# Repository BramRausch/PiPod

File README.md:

# PiPod
PiPod Hardware and Software

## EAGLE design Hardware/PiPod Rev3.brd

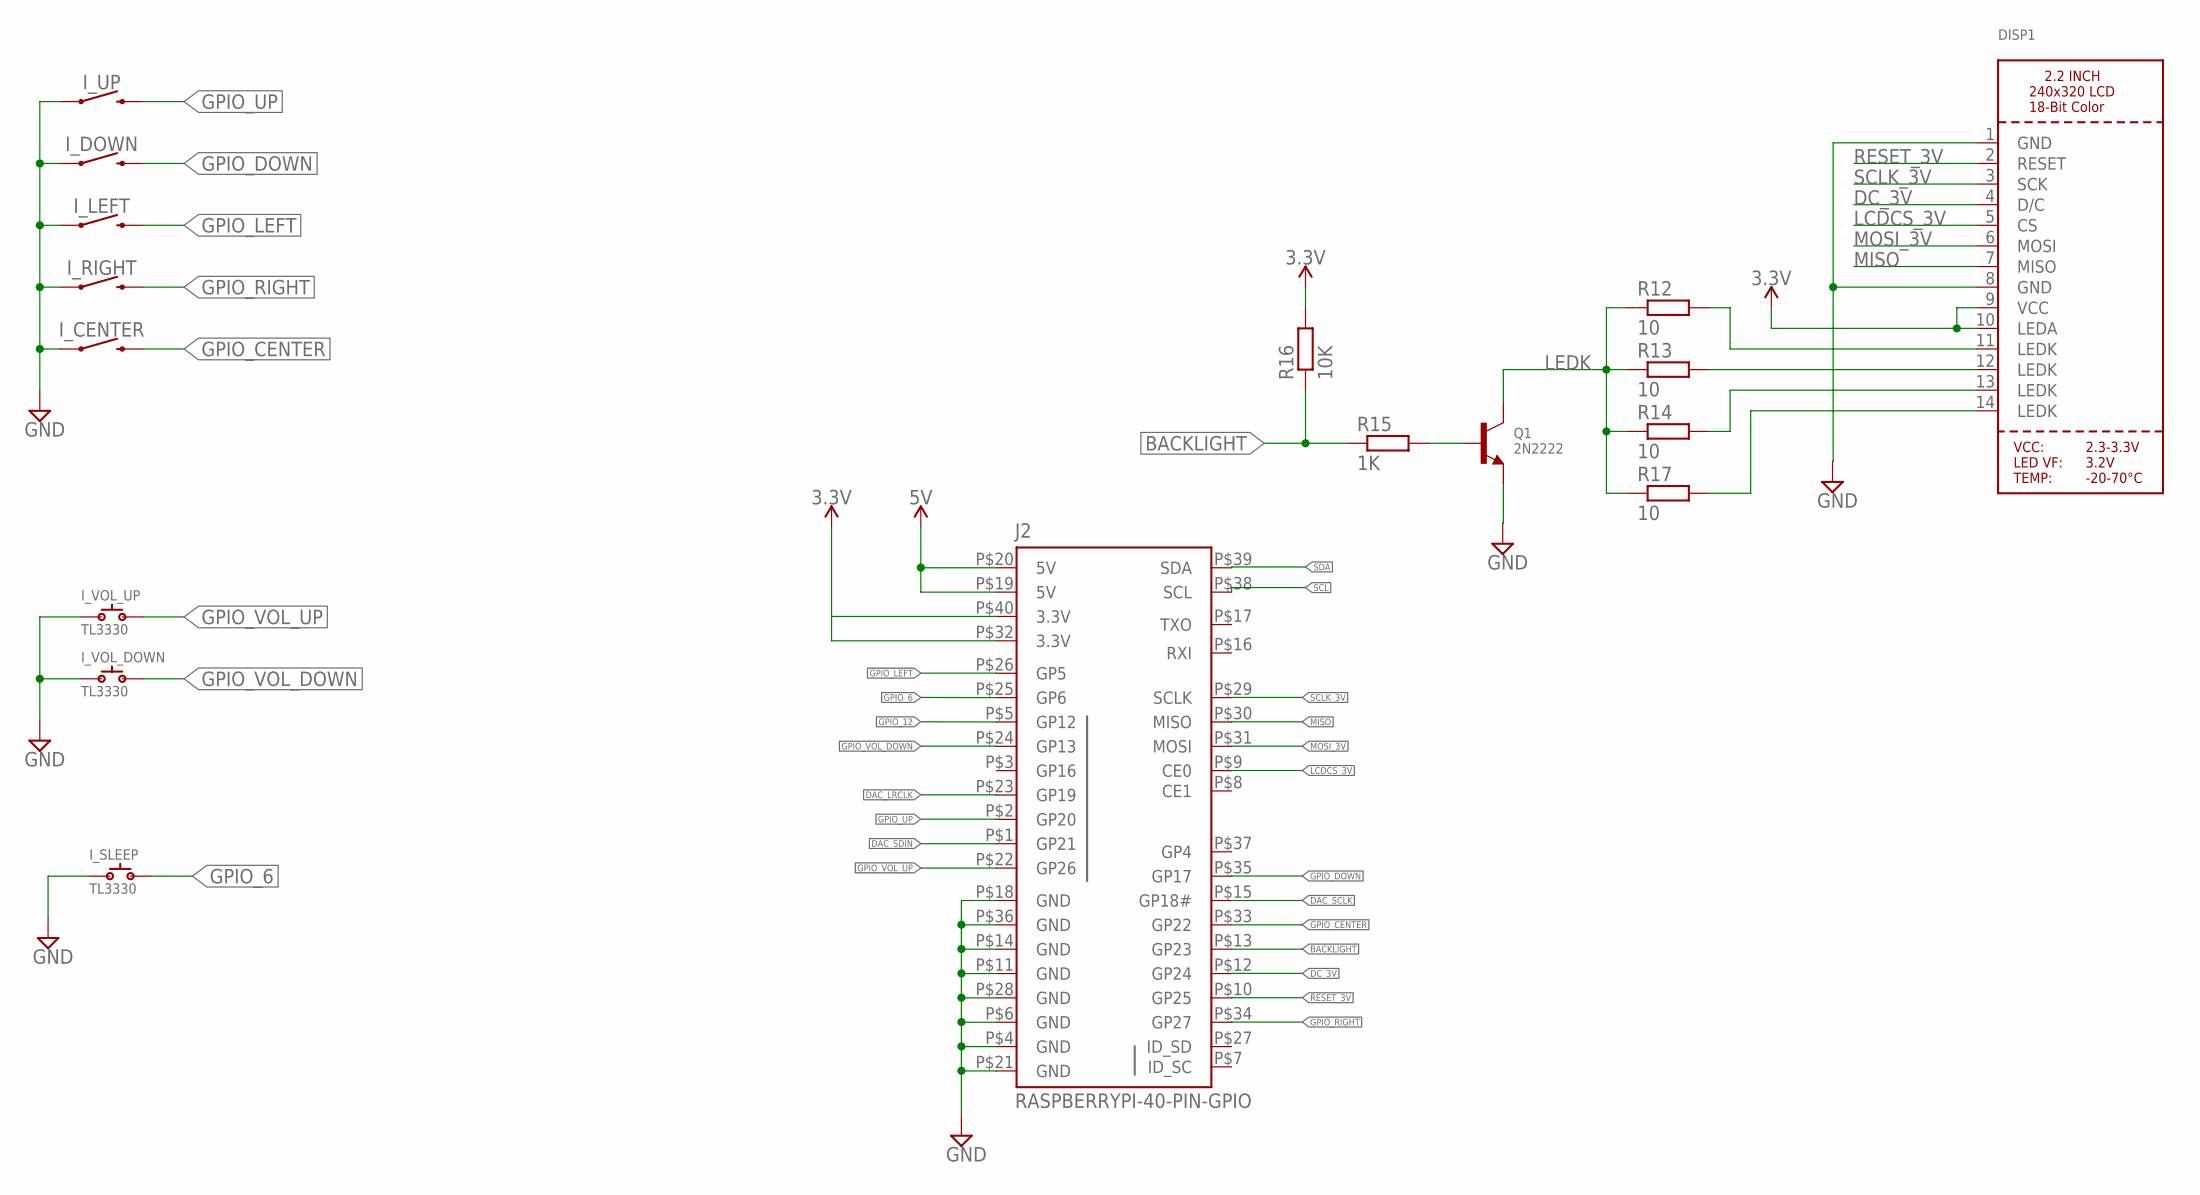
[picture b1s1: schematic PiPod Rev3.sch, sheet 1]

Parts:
DISP1: DISP_LCD_TM022HDH26; TM022HDH26_2.2IN_LCD
I_CENTER: MOMENTARY-SWITCH-SPST-SMD-5.2-REDUNDANT; TACTILE_SWITCH_SMD_5.2MM
I_DOWN: MOMENTARY-SWITCH-SPST-SMD-5.2-REDUNDANT; TACTILE_SWITCH_SMD_5.2MM
I_LEFT: MOMENTARY-SWITCH-SPST-SMD-5.2-REDUNDANT; TACTILE_SWITCH_SMD_5.2MM
I_RIGHT: MOMENTARY-SWITCH-SPST-SMD-5.2-REDUNDANT; TACTILE_SWITCH_SMD_5.2MM
I_SLEEP: TL3330
I_UP: MOMENTARY-SWITCH-SPST-SMD-5.2-REDUNDANT; TACTILE_SWITCH_SMD_5.2MM
I_VOL_DOWN: TL3330
I_VOL_UP: TL3330
J2: RASPBERRYPI-40-PIN-GPIO; 2X20_SMD
Q1: 2N2222; SOT23-WIDE
R12, R13, R14, R17: 10; R0805
R15: 1K; R0805
R16: 10K; R0805

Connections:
3.3V: DISP1.9 (VCC), DISP1.10 (LEDA), J2.P$32 (3.3V), J2.P$40 (3.3V), R16.2; also elsewhere on the board
5V: J2.P$19 (5V), J2.P$20 (5V); also elsewhere on the board
BACKLIGHT: J2.P$13 (GP23), R15.1, R16.1
DAC_LRCLK: J2.P$23 (GP19); also elsewhere on the board
DAC_SCLK: J2.P$15 (GP18#); also elsewhere on the board
DAC_SDIN: J2.P$1 (GP21); also elsewhere on the board
DC_3V: DISP1.4 (D/C), J2.P$12 (GP24)
GND: DISP1.1 (GND), DISP1.8 (GND), I_CENTER.1, I_CENTER.2 (1), I_DOWN.1, I_DOWN.2 (1), I_LEFT.1, I_LEFT.2 (1), I_RIGHT.1, I_RIGHT.2 (1), I_SLEEP.1, I_UP.1, I_UP.2 (1), I_VOL_DOWN.1, I_VOL_UP.1, J2.P$4 (GND), J2.P$6 (GND), J2.P$11 (GND), J2.P$14 (GND), J2.P$18 (GND), J2.P$21 (GND), J2.P$28 (GND), J2.P$36 (GND), Q1.2 (E); also elsewhere on the board
GPIO_6: I_SLEEP.2, J2.P$25 (GP6)
GPIO_12: J2.P$5 (GP12)
GPIO_CENTER: I_CENTER.3 (2), I_CENTER.4 (2), J2.P$33 (GP22)
GPIO_DOWN: I_DOWN.3 (2), I_DOWN.4 (2), J2.P$35 (GP17)
GPIO_LEFT: I_LEFT.3 (2), I_LEFT.4 (2), J2.P$26 (GP5)
GPIO_RIGHT: I_RIGHT.3 (2), I_RIGHT.4 (2), J2.P$34 (GP27)
GPIO_UP: I_UP.3 (2), I_UP.4 (2), J2.P$2 (GP20)
GPIO_VOL_DOWN: I_VOL_DOWN.2, J2.P$24 (GP13)
GPIO_VOL_UP: I_VOL_UP.2, J2.P$22 (GP26)
LCDCS_3V: DISP1.5 (CS), J2.P$9 (CE0)
LEDK: Q1.3 (C), R12.1, R13.1, R14.1, R17.1
MISO: DISP1.7 (MISO), J2.P$30 (MISO)
MOSI_3V: DISP1.6 (MOSI), J2.P$31 (MOSI)
unnamed: DISP1.11 (LEDK), R12.2
unnamed: DISP1.12 (LEDK), R13.2
unnamed: DISP1.13 (LEDK), R14.2
unnamed: Q1.1 (B), R15.2
unnamed: DISP1.14 (LEDK), R17.2
RESET_3V: DISP1.2 (RESET), J2.P$10 (GP25)
SCL: J2.P$38 (SCL); also elsewhere on the board
SCLK_3V: DISP1.3 (SCK), J2.P$29 (SCLK)
SDA: J2.P$39 (SDA); also elsewhere on the board

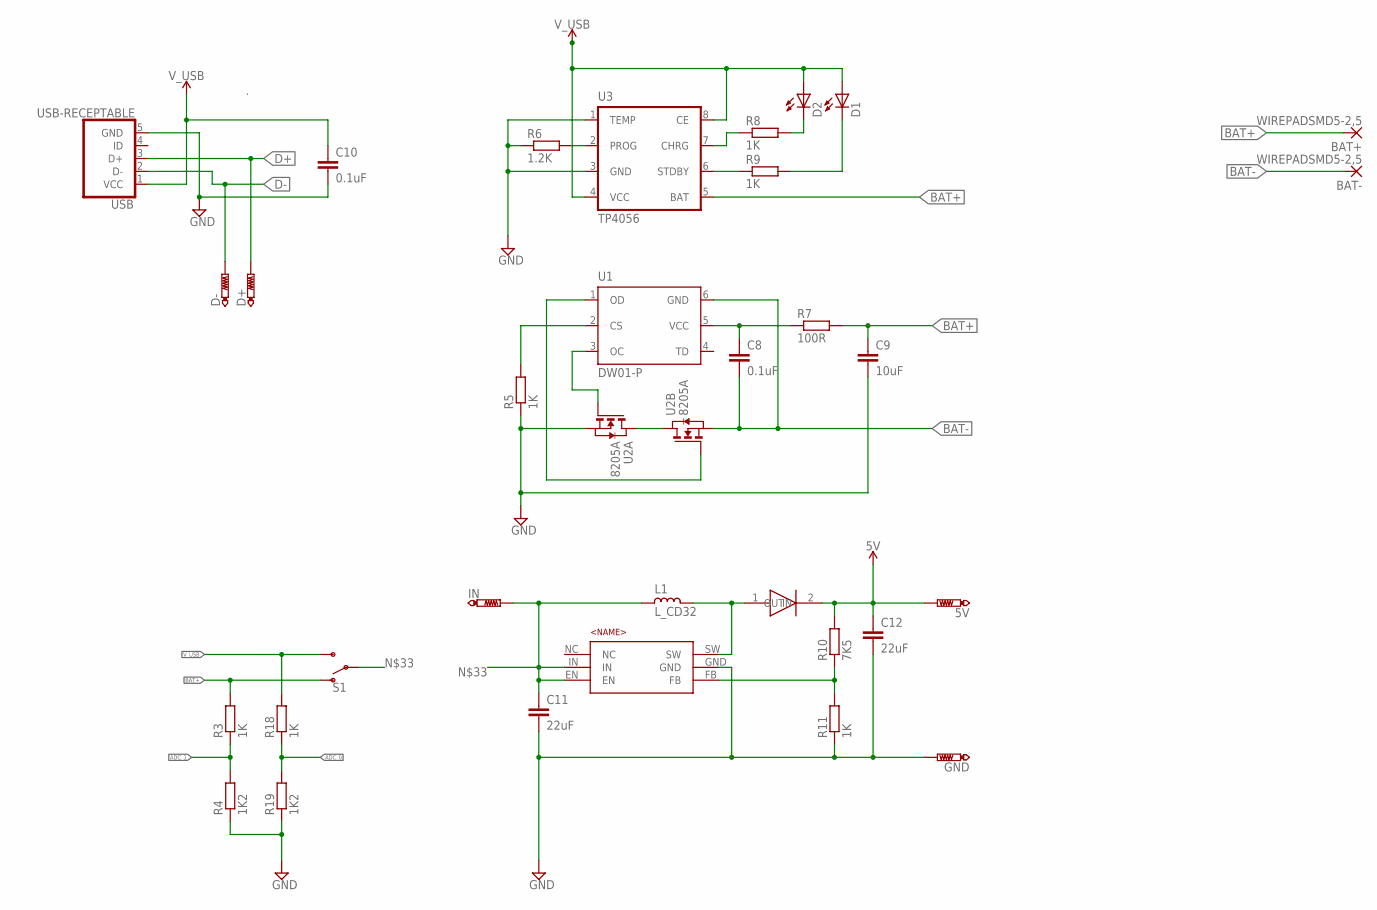
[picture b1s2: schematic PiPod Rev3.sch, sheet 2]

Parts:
5V: PTR1B2,54; B2,54
BAT+: WIREPADSMD5-2,5; 5-2,5
BAT-: WIREPADSMD5-2,5; 5-2,5
C8, C10: 0.1uF; C1206K
C9: 10uF; C1206K
C11, C12: 22uF; C0805K
D1, D2: LEDCHIPLED_0805; CHIPLED_0805
D+: PTR1TP15R; TP15R
D-: PTR1TP15R; TP15R
GND: PTR1B2,54; B2,54
IN: PTR1B2,54; B2,54
L1: L_CD32; CD32
R3, R11, R18: 1K; R0805
R4, R19: 1K2; R0805
R5, R8, R9: 1K; M0805
R6: 1.2K; M0805
R7: 100R; M0805
R10: 7K5; R0805
S1: SWITCH-SPDT-PTH-11.6X4.0MM; SWITCH_SPDT_PTH_11.6X4.0MM
U1: DW01-P; SOT23-6L
U2: 8205A; TSSOP8
U3: TP4056; SO08
U6: MT3608; SOT23-6
U$9: SMA-SS34
USB: USB-RECEPTABLE; FCI-10103594-0001LF

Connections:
5V: 5V.TP, C12.1, R10.2, U$9.2 (OUT); also elsewhere on the board
ADC_0: R18.1, R19.2; also elsewhere on the board
ADC_1: R3.1, R4.2; also elsewhere on the board
BAT+: BAT+.1, C9.1, R3.2, R7.2, S1.1 (O), U3.5 (BAT)
BAT-: BAT-.1, C8.2, U1.6 (GND), U2.6 (S), U2.7 (S)
D+: D+.TP, USB.3 (D+)
D-: D-.TP, USB.2 (D-)
GND: C9.2, C10.2, C11.2, C12.2, GND.TP, R4.1, R5.1, R6.1, R11.1, R19.1, U2.2 (S), U2.3 (S), U3.1 (TEMP), U3.3 (GND), U6.GND, USB.5 (GND); also elsewhere on the board
unnamed: U2.1 (D), U2.8 (D)
unnamed: U1.1 (OD), U2.5 (G)
unnamed: R5.2, U1.2 (CS)
unnamed: R6.2, U3.2 (PROG)
unnamed: U1.3 (OC), U2.4 (G)
unnamed: R9.1, U3.6 (STDBY)
unnamed: C8.1, R7.1, U1.5 (VCC)
unnamed: D2.C, R8.2
unnamed: D1.C, R9.2
unnamed: R8.1, U3.7 (CHRG)
unnamed: L1.1, U6.SW, U$9.1 (IN)
unnamed: R10.1, R11.2, U6.FB
unnamed: C11.1, IN.TP, L1.2, S1.2, U6.EN, U6.IN
V_USB: C10.1, D1.A, D2.A, R18.2, S1.3 (S), U3.4 (VCC), U3.8 (CE), USB.1 (VCC)

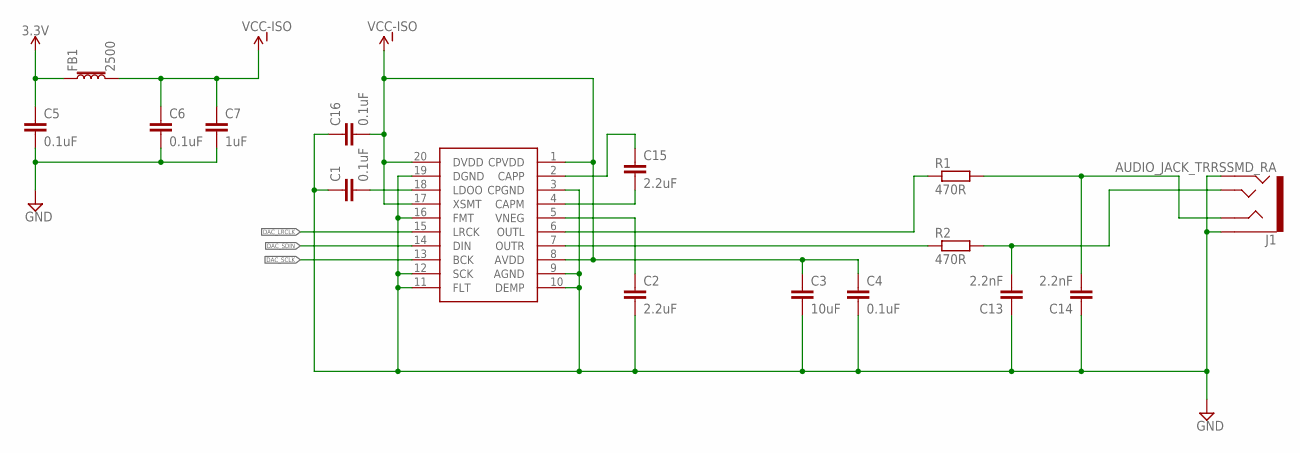
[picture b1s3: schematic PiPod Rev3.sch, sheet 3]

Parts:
C1, C4, C5, C6, C16: 0.1uF; C0805K
C2, C15: 2.2uF; C0805K
C3: 10uF; C0805K
C7: 1uF; C0805K
C13, C14: 2.2nF; C0805K
FB1: 2500; 0603
J1: AUDIO_JACK_TRRSSMD_RA; AUDIO_JACK_3.5MM_TRRS_SMD_RA
R1, R2: 470R; R0805
U5: PCM5102; TSSOP20

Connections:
3.3V: C5.1, FB1.1; also elsewhere on the board
DAC_LRCLK: U5.15 (LRCK); also elsewhere on the board
DAC_SCLK: U5.13 (BCK); also elsewhere on the board
DAC_SDIN: U5.14 (DIN); also elsewhere on the board
GND: C1.1, C2.2, C3.2, C4.2, C5.2, C6.2, C7.2, C13.1, C14.1, C16.1, J1.EARTH, J1.RING2, U5.3 (CPGND), U5.9 (AGND), U5.10 (DEMP), U5.11 (FLT), U5.12 (SCK), U5.16 (FMT), U5.19 (DGND); also elsewhere on the board
unnamed: C1.2, U5.18 (LDOO)
unnamed: C2.1, U5.5 (VNEG)
unnamed: C15.2, U5.4 (CAPM)
unnamed: R2.1, U5.7 (OUTR)
unnamed: R1.1, U5.6 (OUTL)
unnamed: C15.1, U5.2 (CAPP)
unnamed: C13.2, J1.TIP, R2.2
unnamed: C14.2, J1.RING1, R1.2
VCC-ISO: C3.1, C4.1, C6.1, C7.1, C16.2, FB1.2, U5.1 (CPVDD), U5.8 (AVDD), U5.17 (XSMT), U5.20 (DVDD); also elsewhere on the board

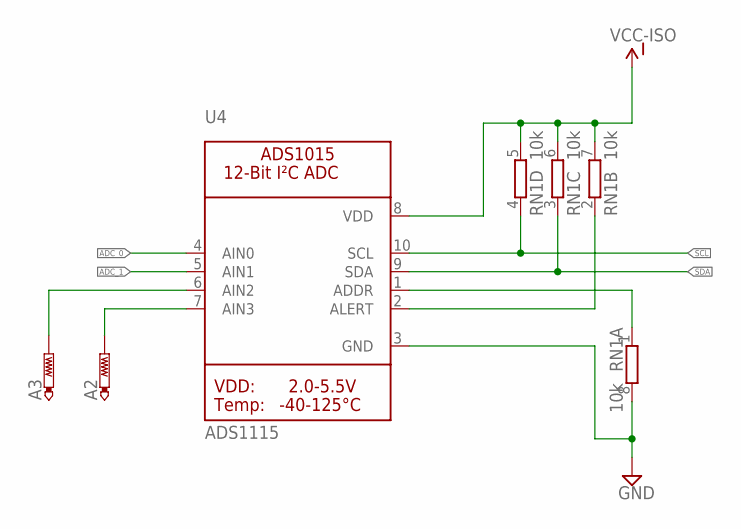
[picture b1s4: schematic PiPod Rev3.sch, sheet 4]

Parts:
A2, A3: PTR1TP15R; TP15R
RN1: 10k; 0603-ARC
U4: ADS1115; MICROBUILDER_MSOP10

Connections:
ADC_0: U4.4 (AIN0); also elsewhere on the board
ADC_1: U4.5 (AIN1); also elsewhere on the board
GND: RN1.8 (2), U4.3 (GND); also elsewhere on the board
unnamed: A2.TP, U4.7 (AIN3)
unnamed: RN1.1, U4.1 (ADDR)
unnamed: RN1.2 (1), U4.2 (ALERT)
unnamed: A3.TP, U4.6 (AIN2)
SCL: RN1.4 (1), U4.10 (SCL); also elsewhere on the board
SDA: RN1.3 (1), U4.9 (SDA); also elsewhere on the board
VCC-ISO: RN1.5 (2), RN1.6 (2), RN1.7 (2), U4.8 (VDD); also elsewhere on the board

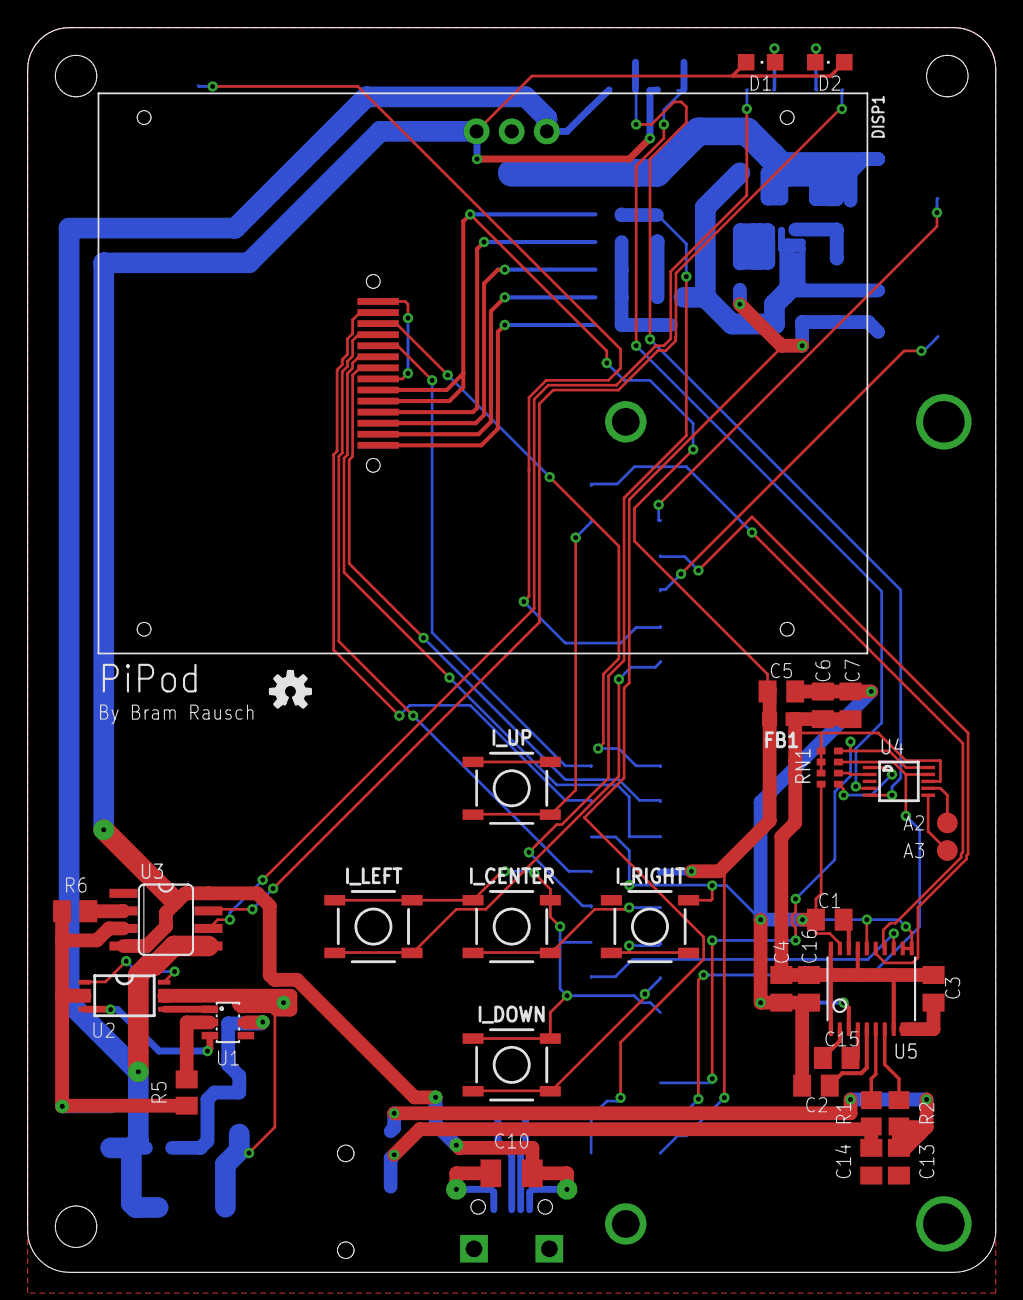
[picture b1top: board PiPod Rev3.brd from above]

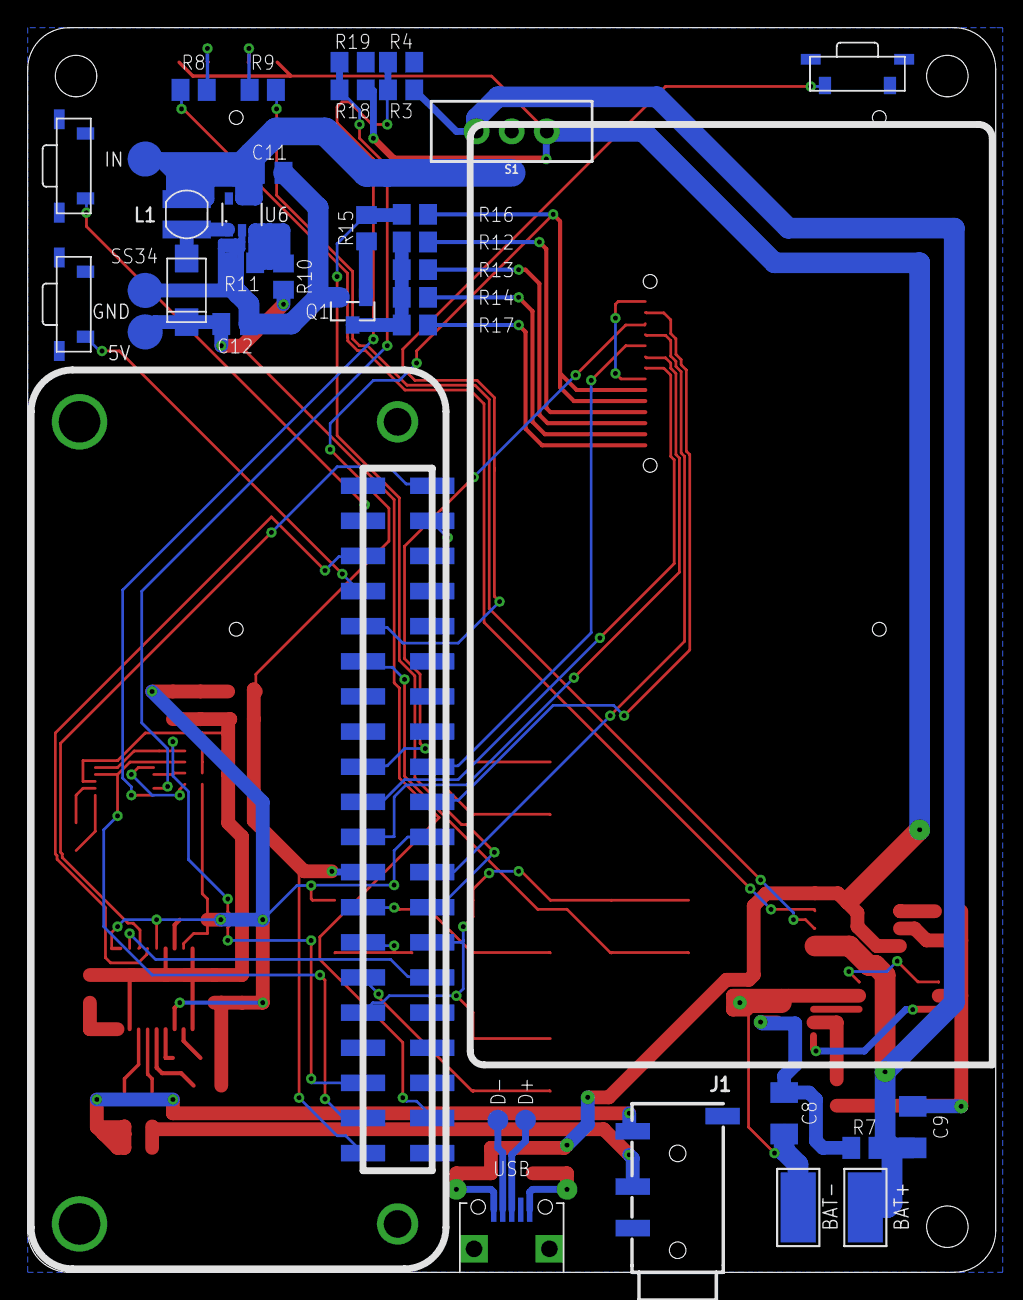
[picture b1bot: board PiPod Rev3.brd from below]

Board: 2 copper layers, 70.0 x 90.0 mm, 71 parts (37 on the bottom side), 62 nets.

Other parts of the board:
E$1: OSHW-LOGO-S

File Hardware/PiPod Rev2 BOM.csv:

"Qty";"Value";"Device";"Package";"Parts";"Description";"MF";"MPN";"OC_FARNELL";"OC_NEWARK";"PROD_ID";"SF_ID";"SF_SKU";"SPICEPREFIX";"TP_SIGNAL_NAME";"VALUE";
"1";"";"DISP_LCD_TM022HDH26";"TM022HDH26_2.2IN_LCD";"DISP1";"TM022HDH26 2.2 Inch 240x320 18-bit LCD - ILI9340C Controller";"";"";"";"";"";"";"";"";"";"";
"2";"";"LEDCHIPLED_0805";"CHIPLED_0805";"D1, D2";"LED";"";"";"";"";"";"";"";"";"";"";
"1";"";"SWITCH-SPDT-PTH-11.6X4.0MM";"SWITCH_SPDT_PTH_11.6X4.0MM";"S1";"Single Pole, Double Throw (SPDT) Switch";"";"";"";"";"SWCH-08261";"";"COM-00102";"";"";"";
"5";"0.1uF";"C-EUC0805K";"C0805K";"C1, C4, C5, C6, C16";"CAPACITOR, European symbol";"";"";"";"";"";"";"";"C";"";"";
"2";"0.1uF";"C-EUC1206K";"C1206K";"C8, C10";"CAPACITOR, European symbol";"";"";"";"";"";"";"";"";"";"";
"1";"1.2K";"R-EU_M0805";"M0805";"R6";"RESISTOR, European symbol";"";"";"";"";"";"";"";"";"";"";
"4";"10";"R-EU_R0805";"R0805";"R12, R13, R14, R17";"RESISTOR, European symbol";"";"";"";"";"";"";"";"";"";"";
"1";"100R";"R-EU_M0805";"M0805";"R7";"RESISTOR, European symbol";"";"";"";"";"";"";"";"";"";"";
"1";"10K";"R-EU_R0805";"R0805";"R16";"RESISTOR, European symbol";"";"";"";"";"";"";"";"";"";"";
"1";"10k";"4R-N0603-ARC";"0603-ARC";"RN1";"Array Chip Resistor";"";"";"unknown";"unknown";"";"";"";"";"";"";
"1";"10uF";"C-EUC0805K";"C0805K";"C3";"CAPACITOR, European symbol";"";"";"";"";"";"";"";"C";"";"";
"1";"10uF";"C-EUC1206K";"C1206K";"C9";"CAPACITOR, European symbol";"";"";"";"";"";"";"";"";"";"";
"3";"1K";"R-EU_M0805";"M0805";"R5, R8, R9";"RESISTOR, European symbol";"";"";"";"";"";"";"";"";"";"";
"4";"1K";"R-EU_R0805";"R0805";"R3, R11, R15, R18";"RESISTOR, European symbol";"";"";"";"";"";"";"";"";"";"";
"2";"1K2";"R-EU_R0805";"R0805";"R4, R19";"RESISTOR, European symbol";"";"";"";"";"";"";"";"";"";"";
"1";"1uF";"C-EUC0805K";"C0805K";"C7";"CAPACITOR, European symbol";"";"";"";"";"";"";"";"C";"";"";
"2";"2.2nF";"C-EUC0805K";"C0805K";"C13, C14";"CAPACITOR, European symbol";"";"";"";"";"";"";"";"C";"";"";
"2";"2.2uF";"C-EUC0805K";"C0805K";"C2, C15";"CAPACITOR, European symbol";"";"";"";"";"";"";"";"C";"";"";
"2";"22uF";"C-EUC0805K";"C0805K";"C11, C12";"CAPACITOR, European symbol";"";"";"";"";"";"";"";"";"";"";
"1";"2500";"FERRITE_BEAD-0603";"0603";"FB1";"Ferrite Bead (blocks, cores, rings, chokes, etc.)";"";"";"";"";"NDUC-07859";"";"";"";"";"30O/1.8A";
"1";"2N2222";"TRANSISTOR_NPNWIDE";"SOT23-WIDE";"Q1";"NPN Transistor";"";"";"";"";"";"";"";"";"";"";
"2";"470R";"R-EU_R0805";"R0805";"R1, R2";"RESISTOR, European symbol";"";"";"";"";"";"";"";"";"";"";
"1";"7K5";"R-EU_R0805";"R0805";"R10";"RESISTOR, European symbol";"";"";"";"";"";"";"";"";"";"";
"1";"8205A";"8205A";"TSSOP8";"U2";"DUAL N-CHANNEL MOSFET";"";"";"";"";"";"";"";"";"";"";
"1";"ADS1115";"MICROBUILDER_ADC_ADS1015";"MICROBUILDER_MSOP10";"U4";"ADS1015 - 12-bit 4-Channel I2C ADC with Internal PGA";"";"";"";"";"";"";"";"";"";"";
"1";"AUDIO_JACK_TRRSSMD_RA";"AUDIO_JACK_TRRSSMD_RA";"AUDIO_JACK_3.5MM_TRRS_SMD_RA";"J1";"Audio Jack - 3.5mm TRRS (SMD)";"";"";"";"";"CONN-10676";"PRT-12639";"";"";"";"";
"1";"DW01-P";"DW01-P";"SOT23-6L";"U1";"One Cell Lithium-ion/Polymer Battery Protection IC";"";"";"";"";"";"";"";"";"";"";
"1";"L_CD32";"L_CD32";"CD32";"L1";"INDUCTOR";"";"";"";"";"";"";"";"";"";"";
"5";"MOMENTARY-SWITCH-SPST-SMD-5.2-REDUNDANT";"MOMENTARY-SWITCH-SPST-SMD-5.2-REDUNDANT";"TACTILE_SWITCH_SMD_5.2MM";"I_CENTER, I_DOWN, I_LEFT, I_RIGHT, I_UP";"Momentary Switch (Pushbutton) - SPST";"";"";"";"";"SWCH-08247";"";"COM-08720";"";"";"";
"1";"MT3608";"MT3608";"SOT23-6";"U6";"";"";"";"";"";"";"";"";"";"";"";
"1";"PCM5102";"PCM5102";"TSSOP20";"U5";"";"";"";"";"";"";"";"";"";"";"";
"3";"PTR1B2,54";"PTR1B2,54";"B2,54";"5V, GND, IN";"TEST PIN";"";"";"";"";"";"";"";"";"";"";
"4";"PTR1TP15R";"PTR1TP15R";"TP15R";"A2, A3, D+, D-";"TEST PIN";"";"";"";"";"";"";"";"";"";"";
"1";"RASPBERRYPI-40-PIN-GPIO";"RASPBERRYPI-40-PIN-GPIO";"2X20_SMD";"J2";"Raspberry Pi GPIO Header";"";"";"";"";"";"";"";"";"";"";
"1";"SMA-SS34";"SMA-SS34";"SMA-SS34";"U$9";"";"";"";"";"";"";"";"";"";"";"";
"3";"TL3330";"TL3330";"TL3330";"I_SLEEP, I_VOL_DOWN, I_VOL_UP";"";"";"";"";"";"";"";"";"";"";"";
"1";"TP4056";"TP4056";"SO08";"U3";"1A Standalone Linear Li-lon Battery Charger with Thermal Regulation";"";"";"";"";"";"";"";"";"";"";
"1";"USB-RECEPTABLE";"USB-RECEPTABLE";"FCI-10103594-0001LF";"USB";"USB Receptable";"";"";"";"";"";"";"";"";"";"";
"2";"WIREPADSMD5-2,5";"WIREPADSMD5-2,5";"5-2,5";"BAT+, BAT-";"Wire PAD connect wire on PCB";"";"";"";"";"";"";"";"";"";"";

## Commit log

2018-08-02 Final version assembly
2018-08-02 Datasheets
2018-08-07 3D files and assembly instruction images from the case
2018-08-16 V1.0 release
    Release V1.0:
    * Current supported filetypes:
    .mp3, .m4a, .wav, .wma
    * New program structure
    * Replaced pygame mixer with VLC player
    * Replaced Eye3d with tagLib

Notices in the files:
parts and their libraries:
SparkFun-Connectors: Licensing: Creative Commons ShareAlike 4.0 International - https://creativecommons.org/licenses/by-sa/4.0
rc-master-smd: Copyright (C) 2007, Bob Starr
